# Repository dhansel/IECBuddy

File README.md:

# IECBuddy

IECBuddy is a USB plug-in for the [C64 RAD Expansion Unit](https://github.com/frntc/RAD), giving the RAD
access to the C64's IEC bus. The IECBuddy is based on my [IECDevice](https://github.com/dhansel/IECDevice)
and [VDrive](https://github.com/dhansel/VDrive) libraries, allowing the RAD to support various disk image 
formats (D64, G64, D71, D81) and fast-load protocols (JiffyDos, Epyx FastLoad, Final Cartridge 3, Action Replay 6,
DolphinDos and SpeedDos). Additionally, the IECBuddy acts as a virtual printer. Printed content can be viewed
on the C64 screen from within the RAD menu.

<br>
  <div align="center">

  </div>
<br>

The IECBuddy comes in four different variants, with differing amounts of components and build effort required:
  * [Barebones](IECBuddy-Barebones) (no PCB, use any RP2040/RP235x module)
  * [Micro](IECBuddy-Micro) (like Barebones but with a PCB and disk change button, requires a RP module pin-compatible with RP2040-One)
  * [Mini](IECBuddy-Mini) (like Micro but with a display and better bus interface, requires a RP module pin-compatible with RP2040-One)
  * [Max](IECBuddy-Max) (like Mini but with parallel cable connector, requires a RP module pin-compatible with Raspberry Pi Pico)

Of course a myriad versions of RP2040 and R235x modules exist. The PCBs for the IECBuddy Micro and Mini variants assume the pinout
of a [RP2040-One](https://www.amazon.com/RP2040-One-Pico-Like-Raspberry-Dual-Core-Processor/dp/B0BMM7SS99). The PCB for the
IECBuddy Max variant assumes the pinout of a Raspberry Pi Pico. The IECBuddy Barebones variant can work with any RP2040 or RP235x module.

To keep things a bit more succinct, in the folling "RP module" stands for "RP2040/RP235x module".

If you have a module with a pinout matching your preferred IECBuddy variant, first check if your module is listed in the UF2 table within the
[uploading the firmware](#uploading-the-firmware) section. If you cannot use one of the provided UF2 firmware files it should still
be fairly easy to [compile and upload](software/IECBuddy/README.md) the firmware yourself.

The IECBuddy stores files and disk images in the RP module's flash memory. One MB of flash memory is used for the
firmware itself, the remainder can be used for storing disk images. One MB of flash memory can hold about six D64 disk images.
Note that disk images can easily be transferred between the RAD and the IECBuddy so the IECBuddy does not need to hold all
your disk images at the same time.

The IECBuddy can plug directly into a RAD powered by a Raspberry Pi 3. If your RAD uses a Raspberry Pi Zero then 
you will need [an adapter cable](https://www.raspberrypi.com/products/micro-usb-male-to-usb-a-female-cable/) 
to connect the IECBuddy since the Zero only has a micro-USB OTG port.

To build an IECBuddy, select and build whichever variant appeals to you and then follow the instructions in the
[Uplodading the firmware](#uploading-the-firmware) section below.

## IECBuddy Barebones

The barebones variant is the simplest version, requiring no manufactured PCB. While the pictures shown here use
a [RP2040-One](https://www.amazon.com/RP2040-One-Pico-Like-Raspberry-Dual-Core-Processor/dp/B0BMM7SS99) module, any
RP module should work. Additionally you will need a Commodore [serial cable](https://www.c64-wiki.com/wiki/Serial_Port)
connector. Either solder the cable directly to the RP module or set it up on a breadboard:

<br>
  <div align="center">

  </div>
<br>

Connect the Commodore serial cable to the RP module as follows:

IEC Bus Pin | Signal   | RP module
------------|----------|-----------
1           | SRQ      | Not connected 
2           | GND      | GND
3           | ATN      | GPIO2
4           | CLK      | GPIO3 
5           | DATA     | GPIO4 
6           | RESET    | GPIO5 

Then [upload the IECBuddy Micro firmware](#uploading-the-firmware) to the RP module and you're good to go.
Downsides are that there is no display and no "Disk Change" button.
If you would like a "Disk Change" button, simply wire a pushbutton switch between pins GND and GPIO8 on the RP module.

Note that this connects the 5V IEC bus lines directly to the RP module inputs. There are varying
opinions online on whether or not this can damage the RP and/or whether the RP is
capable of properly driving the IEC bus lines (especially when multiple devices are connected).
In my testing I have not had any problems, even with multiple other devices connected. YMMV.

If you would prefer proper voltage conversion and line drivers then use the "Mini" version below.

## IECBuddy Micro

<br>
  <div align="center">

  </div>
<br>

If you would like a somewhat cleaner and more permanent build but still want to go with a very small
footprint and minimal component count, use the "IECBuddy Micro" variant. This PCB requires a RP
module that is pin-compatible with the RP2040-One. Check the [Uplodading the firmware](#uploading-the-firmware) 
section below to see which RP modules are supported.

You can either solder the serial cable directly onto the board (connections are labeled on the board) or solder a 
proper IEC connector onto the board and use a standard serial cable. This also comes with
space for a pushbutton switch. No display though.

The same caveats regarding voltage conversion and line drivers apply as described in the "Barebones" section above.

A Gerber file for PCB production can be downloaded [here](https://github.com/dhansel/IECBuddy/raw/refs/heads/main/hardware/IECBuddy-micro-gerber.zip).<br>
A PDF file with the schematics is available [here](https://github.com/dhansel/IECBuddy/raw/refs/heads/main/hardware/IECBuddy-micro-schematic.pdf).<br>
KiCad files for the board are [here](hardware/IECBuddy-micro).

You will need the following components (the given links are just suggestions, I do not get any kickbacks for them).

Designator | Component 
-----------|-----------
U1         | [RP2040-One](https://www.amazon.com/RP2040-One-Pico-Like-Raspberry-Dual-Core-Processor/dp/B0BMM7SS99)
SW1        | [Pushbutton Switch](https://www.digikey.com/en/products/detail/c-k/PTS645VH58-2-LFS/1146783)
IEC1       | [IEC Bus Connector (6 Pin)](https://www.aliexpress.us/item/3256807108500271.html)

You can skip the IEC1 connector if you solder the serial cable directly to the board (connections on the board are labeled).

## IECBuddy Mini

  <div align="center">

  </div>

The Mini variant is slightly larger than the Micro version and requires more components besides
the RP module. As a result it comes with the following features that are not present in the smaller versions:

First, it has space and connections on the PCB for a [1.3" TFT display](https://www.aliexpress.us/item/3256805899270213.html).
The display shows the currently mounted disk image as well as disk status and progress bars while loading.

Second, it uses 7406 and 74LVC04 ICs for voltage conversion and properly interfacing with and driving the Commodore IEC bus lines.
This is very similar to the way original hardware (like the 1541) interfaces to the IEC bus. It also protects the RP
from the possible overcurrent and overvoltage conditions described in the "Barebones" section above.

Like the Micro variant, this PCB requires a RP module that is pin-compatible with the RP2040-One. 
Check the [Uplodading the firmware](#uploading-the-firmware) section below to see which RP modules are supported.

A Gerber file for PCB production can be downloaded [here](https://github.com/dhansel/IECBuddy/raw/refs/heads/main/hardware/IECBuddy-mini-gerber.zip).<br>
A PDF file with the schematics is available [here](https://github.com/dhansel/IECBuddy/raw/refs/heads/main/hardware/IECBuddy-mini-schematic.pdf).<br>
KiCad files for the board are [here](hardware/IECBuddy-mini).

You will need the following components (the given links are just suggestions, I do not get any kickbacks for them).

Designator | Component 
-----------|-----------
R1,R2,R3,R4| [Resistor 1kOhm SMD0805](https://www.digikey.com/en/products/detail/stackpole-electronics-inc/RMCF0805FT1K00/1760090)
C1,C2      | [Ceramic Capacitor 100nF SMD0805](https://www.digikey.com/en/products/detail/kyocera-avx/KGM21NR71H104KT/563505)
U1         | [RP2040-One](https://www.amazon.com/RP2040-One-Pico-Like-Raspberry-Dual-Core-Processor/dp/B0BMM7SS99)
U2         | [74LVC04AD SOIC](https://www.digikey.com/en/products/detail/nexperia-usa-inc/74LVC04AD-118/946673)
U3         | [7406DR SOIC](https://www.digikey.com/en/products/detail/texas-instruments/SN7406DR/276661)
SW1        | [Pushbutton Switch](https://www.digikey.com/en/products/detail/c-k/PTS645VH58-2-LFS/1146783)
ST7789     | [TFT Display](https://www.aliexpress.us/item/3256805899270213.html)
IEC1       | [IEC Bus Connector (6 Pin)](https://www.aliexpress.us/item/3256807108500271.html)

Various components can be left out if desired:
  * You can leave out the IEC1 connector if you solder the serial cable directly to the board (connections on the board are labeled).
  * You can leave out the ST7789 display if you don't want a display.
  * If you don't want to use the IEC bus driver ICs then you can place solder on the JP1-JP5 solder jumpers and leave out R1-R4, C1, C2, U2 and U3 (in this case use the IECBuddyMicro.uf2 firmware).

I recommend uploading the firmware **before** soldering on the display. The display sits on top of the RP module, which
makes accessing the "Boot" button (required for firmware upload) tricky - still possible, but a bit fiddly.

## IECBuddy Max

The IECBuddy Max variant has a much larger PCB layout and uses a Raspberry Pi Pico (version 1 or 2).
It has all the features of the Mini version and additionally a second IEC port for daisy-chaining 
and a connector for a parallel cable to be used with Dolphin Dos and Speed Dos.
Descriptions on how to make a compatible parallel cable and user port connector can be found in
various places over the internet, for example
[here](https://github.com/dhansel/IECDevice/tree/main/hardware#user-port-breakout-board),
[here](https://github.com/svenpetersen1965/1541-parallel-adapter-SpeedDOS)
or [here](https://github.com/FraEgg/commodore-1541-parallel-port-adapter-c64-c128-speeddos-dolphindos)

  <div align="center">

  </div>

A Gerber file for PCB production can be downloaded [here](https://github.com/dhansel/IECBuddy/raw/refs/heads/main/hardware/IECBuddy-max-gerber.zip).<br>
A PDF file with the schematics is available [here](https://github.com/dhansel/IECBuddy/raw/refs/heads/main/hardware/IECBuddy-max-schematic.pdf).<br>
KiCad files for the board are [here](hardware/IECBuddy-max).

This PCB requires a RP module that is pin-compatible with the Raspberry Pi Pico. 
Check the [Uplodading the firmware](#uploading-the-firmware) section below to see which RP modules are supported.

You will need the following components (the given links are just suggestions, I do not get any kickbacks for them).

Designator | Component 
-----------|-----------
R1,R2,R3,R4| [Resistor 1kOhm SMD0805](https://www.digikey.com/en/products/detail/stackpole-electronics-inc/RMCF0805FT1K00/1760090)
C1,C2,C3   | [Ceramic Capacitor 100nF SMD0805](https://www.digikey.com/en/products/detail/kyocera-avx/KGM21NR71H104KT/563505)
U1         | [Raspberry Pi Pico](https://www.microcenter.com/product/661033/raspberry-pi-pico-microcontroller-development-board)
U2         | [74CBTD3861DW](https://www.digikey.com/en/products/detail/texas-instruments/SN74CBTD3861DW/378015)
U3         | [74LVC04AD SOIC](https://www.digikey.com/en/products/detail/nexperia-usa-inc/74LVC04AD-118/946673)
U4         | [7406DR SOIC](https://www.digikey.com/en/products/detail/texas-instruments/SN7406DR/276661)
Reset,DiskChg | [Pushbutton Switch](https://www.digikey.com/en/products/detail/same-sky-formerly-cui-devices-/TS02-66-60-BK-100-LCR-D/15634327)
ST7789     | [TFT Display](https://www.aliexpress.us/item/3256805899270213.html)
IEC1       | [IEC Bus Connector (6 Pin)](https://www.aliexpress.us/item/3256807108500271.html)
Parallel1, Parallel2 | [10-position IDC Connector](https://www.digikey.com/en/products/detail/on-shore-technology-inc/302-S101/2178422)

## Uploading the firmware

Pre-compiled versions of the firmware are available for all four versions of the IECBuddy and a variety of RP modules. 

If your RP module is included in the table below then programming is trivial. First, download the UF2 file appropriate for your IECBuddy variant and RP module
("---" in the table means "not supported because the RP module does not match the PCB"):

IECBuddy   | [RP2040-One](https://www.amazon.com/RP2040-One-Pico-Like-Raspberry-Dual-Core-Processor/dp/B0BMM7SS99) <br> (4MB flash) | [RP2350-One](https://www.ebay.com/itm/286217752456) <br> (4MB flash) | [TENSTAR RP2350](https://aliexpress.com/item/1005008622261552.html) <br> (16MB flash) | Pi Pico <br> (2MB flash) | Pi Pico 2 <br> (4MB flash) | [Purple Pico](https://de.aliexpress.com/item/1005005594351599.html) <br> (16MB flash)
-----------|------------|------------|-------------------|----------------|---------------------|---------------------
Barebones  | [UF2](https://github.com/dhansel/IECBuddy/raw/refs/heads/main/software/IECBuddyMicro2040One.uf2) | [UF2](https://github.com/dhansel/IECBuddy/raw/refs/heads/main/software/IECBuddyMicro2350One.uf2) | [UF2](https://github.com/dhansel/IECBuddy/raw/refs/heads/main/software/IECBuddyMicroTenstar2350.uf2) | [UF2](https://github.com/dhansel/IECBuddy/raw/refs/heads/main/software/IECBuddyMicroPico1.uf2) | [UF2](https://github.com/dhansel/IECBuddy/raw/refs/heads/main/software/IECBuddyMicroPico2.uf2) | [UF2](https://github.com/dhansel/IECBuddy/raw/refs/heads/main/software/IECBuddyMicroPurplePico.uf2)
Micro      | [UF2](https://github.com/dhansel/IECBuddy/raw/refs/heads/main/software/IECBuddyMicro2040One.uf2) | [UF2](https://github.com/dhansel/IECBuddy/raw/refs/heads/main/software/IECBuddyMicro2350One.uf2) | [UF2](https://github.com/dhansel/IECBuddy/raw/refs/heads/main/software/IECBuddyMicroTenstar2350.uf2) | --- | --- | ---
Mini       | [UF2](https://github.com/dhansel/IECBuddy/raw/refs/heads/main/software/IECBuddyMini2040One.uf2) | [UF2](https://github.com/dhansel/IECBuddy/raw/refs/heads/main/software/IECBuddyMini2350One.uf2)  | [UF2](https://github.com/dhansel/IECBuddy/raw/refs/heads/main/software/IECBuddyMiniTenstar2350.uf2)  | --- | --- | ---
Max        | --- | --- | --- | [UF2](https://github.com/dhansel/IECBuddy/raw/refs/heads/main/software/IECBuddyMaxPico1.uf2) | [UF2](https://github.com/dhansel/IECBuddy/raw/refs/heads/main/software/IECBuddyMaxPico2.uf2) | ---

Then:
  1) Connect the USB connector of the RP module to your computer in "boot" mode. This can be done in two ways:
     - Make the connection to the computer **while holding down the "Boot" button on the device**. Note that this can be tricky
       for the Mini version if you have already soldered the display since the display obstructs access to the RP2040-One.
     - Just connect the RP module without holding the "Boot" button down. This will register a new serial (COM) port on your computer.
       Download [SKTool.exe](https://github.com/dhansel/IECBuddy/raw/refs/heads/main/software/SKTool/SKTool.exe) and run it with the following parameters: `SKTool -p COMx boot` (where COMx is the new COM port).
       Alternatively, start a terminal program (e.g. TeraTerm, Putty or even the serial monitor in the Arduino IDE) and connect
       to the new COM port with a baud rate of 1200.
     As a result of either of these, your computer should now show a new external drive.
  2) Copy the downloaded UF2 file to the root directory of the new drive.
  3) Disconnect the RP module from your computer.

If your RP module is not included in the table above and/or you would like to compile the firmware yourself, instructions can be found [here](software/IECBuddy/README.md). 

## Usage

When it is connected to the RAD (via USB) and C64 (via serial cable), the IECBuddy behaves like a disk drive.
The initial device number is 8 but can be configured from within the RAD menu system.

The IECBuddy is based on the [IECDevice library](https://github.com/dhansel/IECDevice) and therefore supports the 
same fastload protocols: JiffyDos, Epyx FastLoad, Final Cartridge 3, Action Replay 6, DolphinDos and SpeedDos.
Games that use their own fastload protocols will likely not work, the IECBuddy will report error "M-E not supported"
and the on-board LED will blink quickly (5Hz as opposed to 2Hz for a regular error).

Loading the directory shows all files and disk images currently on the IECBuddy file system. You can use "CD"
to enter and exit disk images. If you have a DOS wedge (like in JiffyDos), `@CD:GAMES.D64` will enter the GAMES.D64
Disk image, `@CD/` will exit the image and go back to the top-level directory. If you do not have a DOS wedge, 
doing a `LOAD"GAMES.D64",8` will automatically switch into the GAMES.D64 disk image and load its directory,
`LOAD"/",8` will return to the top level.

If desired, a new disk image can be created by using the "N" command, for examplem, executing `@N:GAMES2.D64`
in the top-level dierctory will create a new disk image named GAMES2.D64.

Files (either PRG files or disk images) can be copied between the IECBuddy and the RAD's SD card via the RAD menu system.
To enter the [IECBuddy submenu](https://github.com/frntc/RAD#iecbuddy-submenu) on the RAD, press "I" within the RAD main menu.

<br>
  <div align="center">
  
  </div>
<br>

The IECBuddy also emulates a printer, more specifically a STAR NL-10 printer with device number 4. The STAR NL-10 was
compatible with Commodore MPS-801 commands as well as the EPSON FX-80 command set. Much of the existing C64 software
supports either one of these (if not specifically the NL-10) and should therefore be compatible.

After printing, enter the RAD menu to see a preview of the printout and/or copy a BMP or PDF version of the printed
content to the RAD's SD card.

<br>
  <div align="center">
  
  </div>
<br>

For more information on the RAD menu structure relating to the IECBuddy see [here](https://github.com/frntc/RAD#iecbuddy-submenu).

As an alternative to copying files via the RAD menu interface you can use connect the IECBuddy to your PC 
and use [SKTool](software/SKTool) to manage the files directly.

## Firmware revisions

The following IECBuddy firmware revisions have been released:

  - **1.0** (January 26, 2026)
    - Initial release
   
  - **1.01** (March 16, 2026)
    - Support ",A" (append) file open mode in main directory
    - If a file is created in the main directory and the file has a known extension (PRG, SEQ, D64, D71, D81, G64, G71) then do not add an additional .PRG extension
    - Fixed JiffyDos protocol timing issue when transmitting EOI in single-byte protocol
    - Fixed support of "XF-" and "XF+" commands in DolphinDos

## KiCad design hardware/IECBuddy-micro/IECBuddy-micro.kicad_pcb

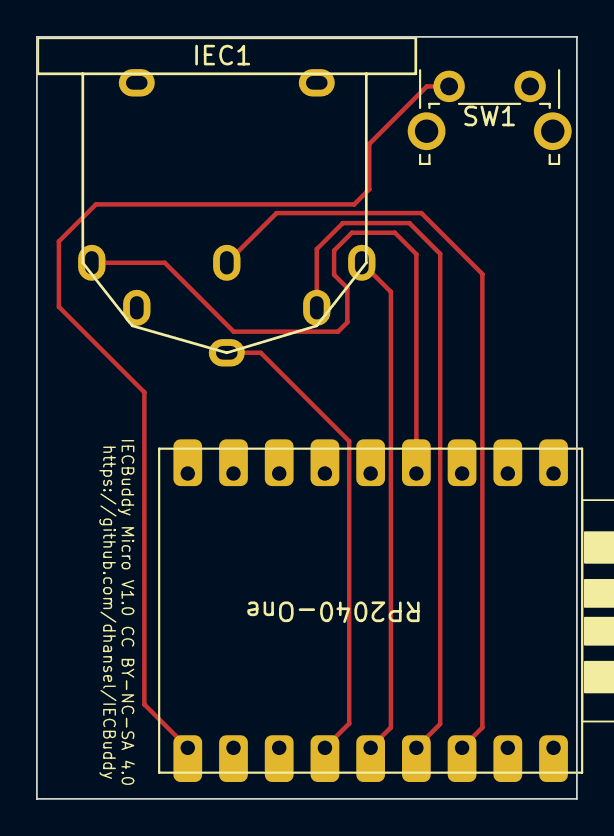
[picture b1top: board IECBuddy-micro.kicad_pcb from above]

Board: 2 copper layers, 30.0 x 42.3 mm, 5 parts (0 on the bottom side), 7 nets.

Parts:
IEC1: SDS-60J; C64_IEC
MH1, MH2: ZipTie; ZipTie_3.0mm
SW1: DskChg; SW_Tactile_SPST_Angled_PTS645Vx83-2LFS
U1: RP2040-One; RP2040-One-Sidesonly

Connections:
ATN: IEC1.3, U1.16 (GP2)
CLK: IEC1.4, U1.15 (GP3)
DATA: IEC1.5, U1.14 (GP4)
GND: IEC1.2, IEC1.E1 (GND), IEC1.E2 (GND__1), SW1.2, U1.2 (GND)
unnamed: SW1.1, U1.10 (GP8)
RST: IEC1.6, U1.13 (GP5)
SRQ: IEC1.1, U1.4 (GP29)

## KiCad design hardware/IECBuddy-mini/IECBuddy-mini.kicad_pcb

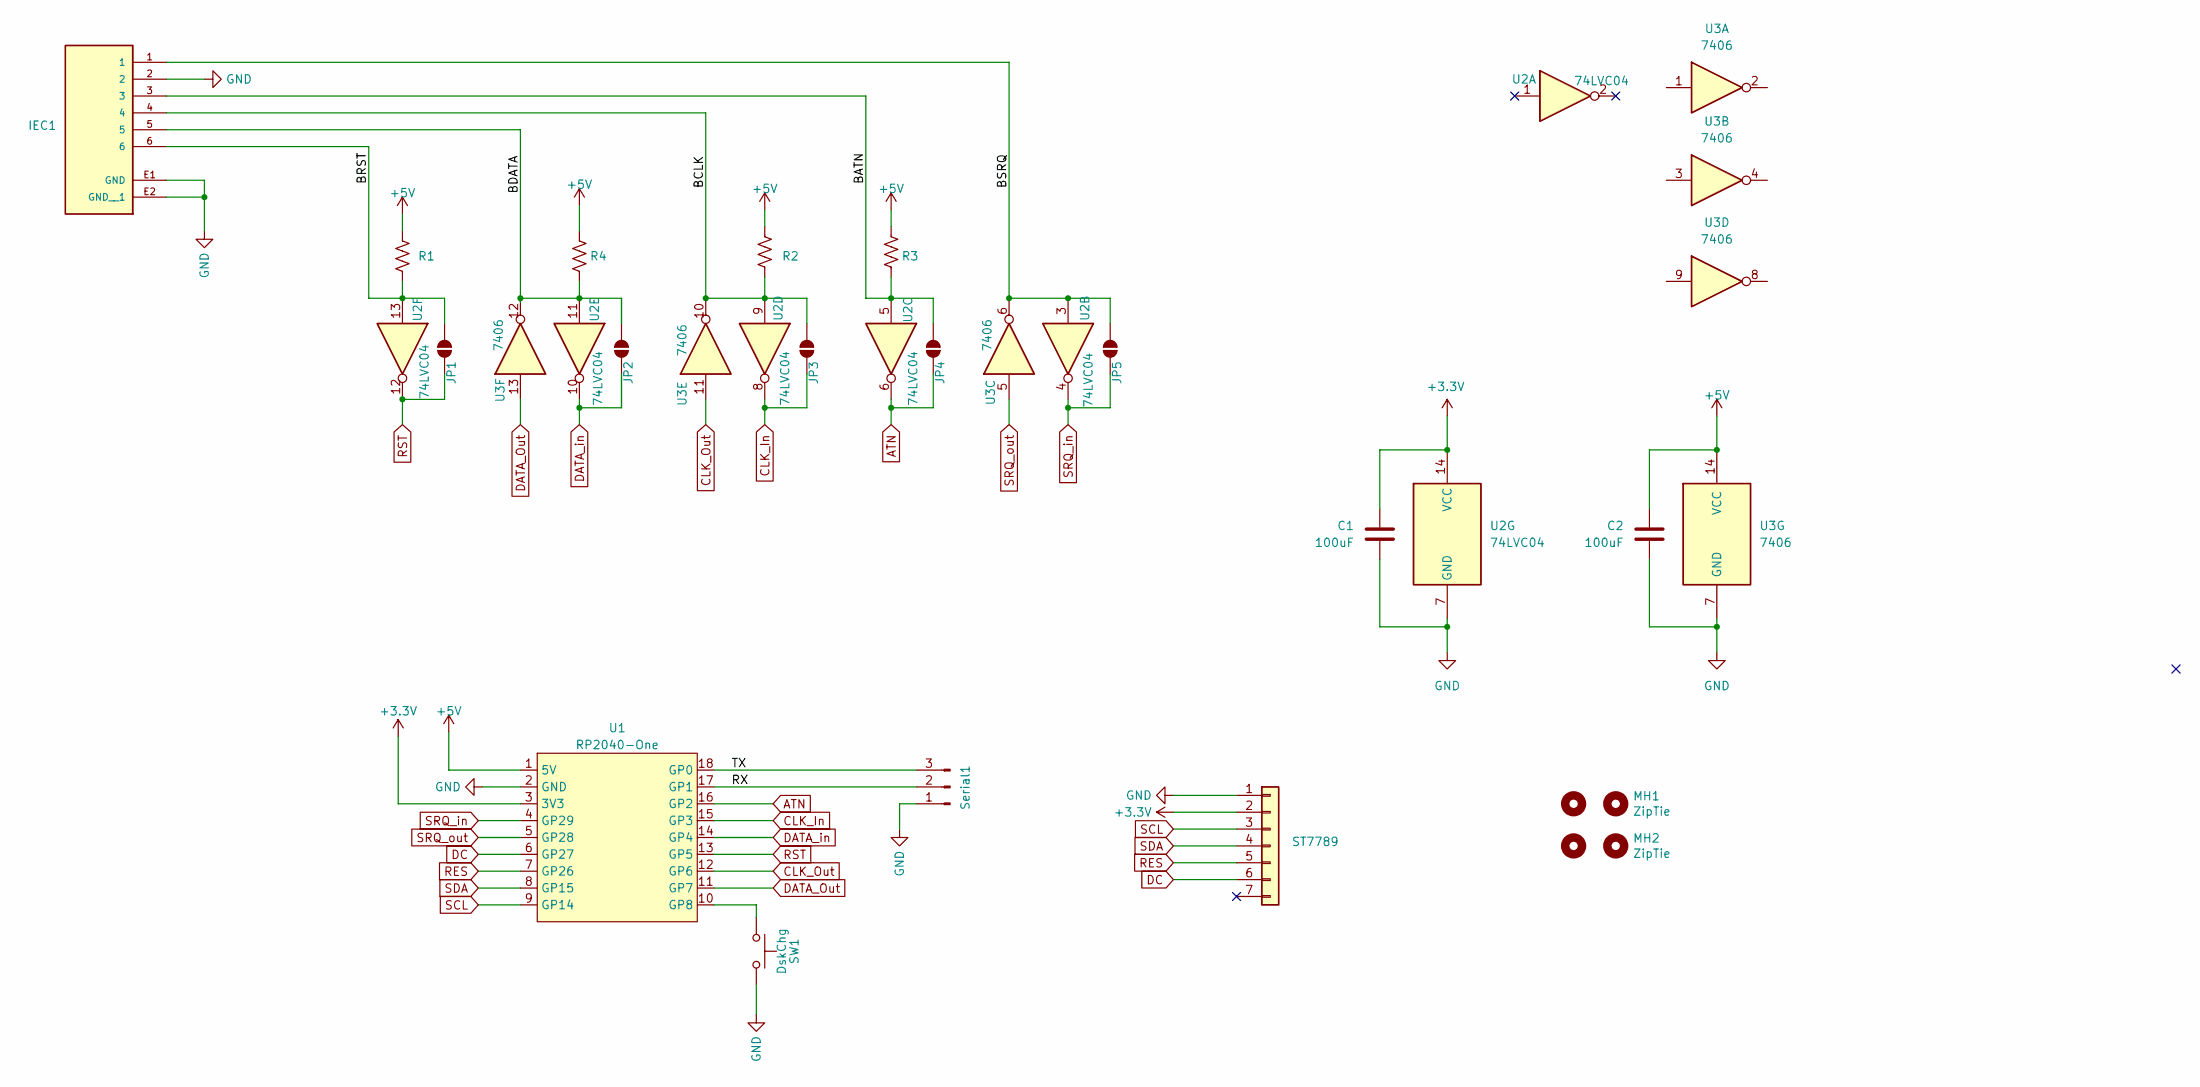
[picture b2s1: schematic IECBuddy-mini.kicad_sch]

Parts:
C1, C2: 100uF; C_0805_2012Metric_Pad1.18x1.45mm_HandSolder
H1, H2: MountingHole; MountingHole_3.2mm_M3
IEC1: SDS-60J; C64_IEC; PARTREV 1.06/02-13-2020
JP1, JP2, JP3, JP4, JP5: SolderJumper_2_Open; SolderJumper-2_P1.3mm_Open_Pad1.0x1.5mm
MH1, MH2: ZipTie; ZipTie_3.0mm
R1, R2, R3, R4: 1k; R_0805_2012Metric
ST7789: ST7789; PinHeader_1x07_P2.54mm_Vertical
SW1: DskChg; SW_Tactile_SPST_Angled_PTS645Vx83-2LFS
Serial1: Serial1; PinSocket_1x03_P2.54mm_Vertical
U1: RP2040-One; RP2040-One-Sidesonly
U2: 74LVC04; SOIC-14_3.9x8.7mm_P1.27mm
U3: 7406; SOIC-14_3.9x8.7mm_P1.27mm

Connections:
+3.3V: C1.1, ST7789.2, U1.3 (3V3), U2.14 (VCC)
+5V: C2.1, R1.1, R2.1, R3.1, R4.1, U1.1 (5V), U3.14 (VCC)
/BATN: IEC1.3, JP4.2 (B), R3.2, U2.5
/BCLK: IEC1.4, JP3.2 (B), R2.2, U2.9, U3.10
/BDATA: IEC1.5, JP2.2 (B), R4.2, U2.11, U3.12
/BRST: IEC1.6, JP1.2 (B), R1.2, U2.13
/BSRQ: IEC1.1, JP5.2 (B), U2.3, U3.6
/RX: Serial1.2, U1.17 (GP1)
/TX: Serial1.3, U1.18 (GP0)
ATN: JP4.1 (A), U1.16 (GP2), U2.6
CLK_In: JP3.1 (A), U1.15 (GP3), U2.8
CLK_Out: U1.12 (GP6), U3.11
DATA_Out: U1.11 (GP7), U3.13
DATA_in: JP2.1 (A), U1.14 (GP4), U2.10
DC: ST7789.6, U1.6 (GP27)
GND: C1.2, C2.2, IEC1.2, IEC1.E1 (GND), IEC1.E2 (GND__1), ST7789.1, SW1.2, Serial1.1, U1.2 (GND), U2.7 (GND), U3.7 (GND)
unnamed: SW1.1, U1.10 (GP8)
RES: ST7789.5, U1.7 (GP26)
RST: JP1.1 (A), U1.13 (GP5), U2.12
SCL: ST7789.3, U1.9 (GP14)
SDA: ST7789.4, U1.8 (GP15)
SRQ_in: JP5.1 (A), U1.4 (GP29), U2.4
SRQ_out: U1.5 (GP28), U3.5

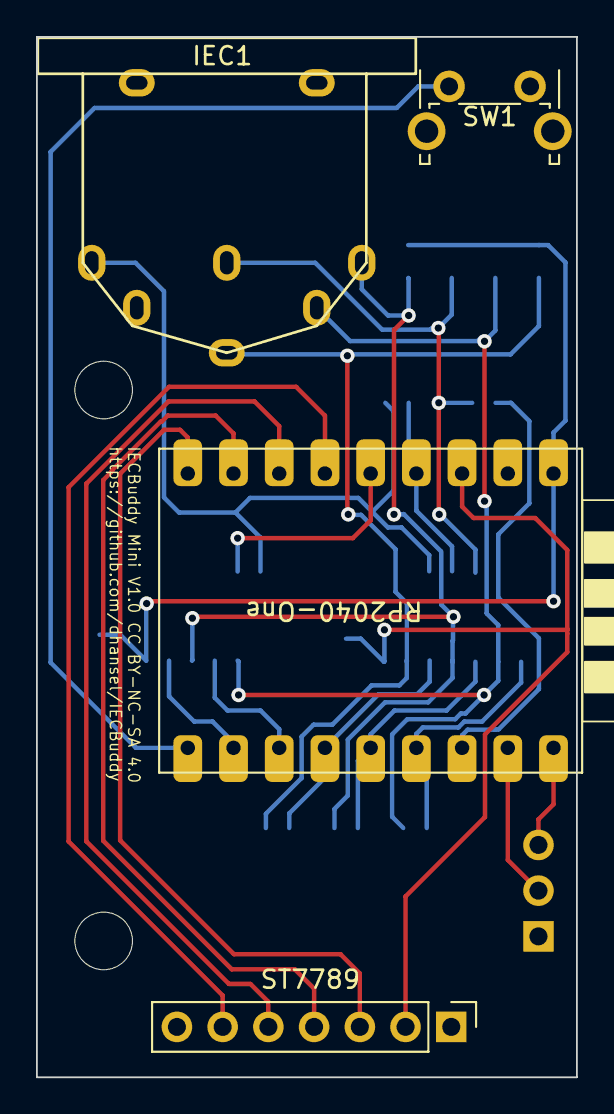
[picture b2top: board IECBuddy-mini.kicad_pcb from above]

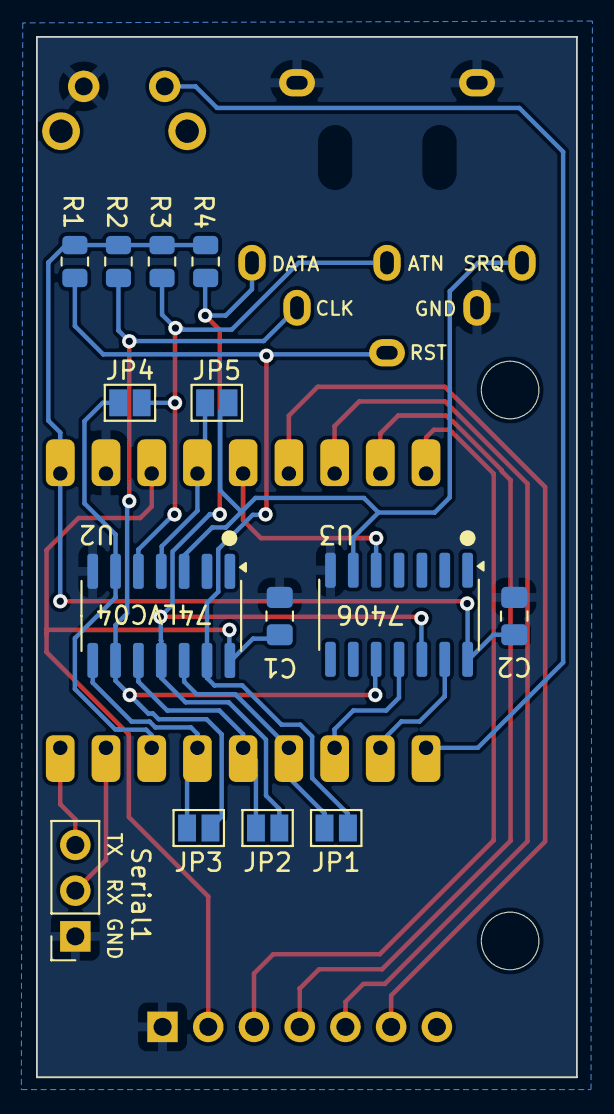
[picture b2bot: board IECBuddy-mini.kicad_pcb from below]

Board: 2 copper layers, 30.0 x 57.8 mm, 22 parts (14 on the bottom side), 23 nets.

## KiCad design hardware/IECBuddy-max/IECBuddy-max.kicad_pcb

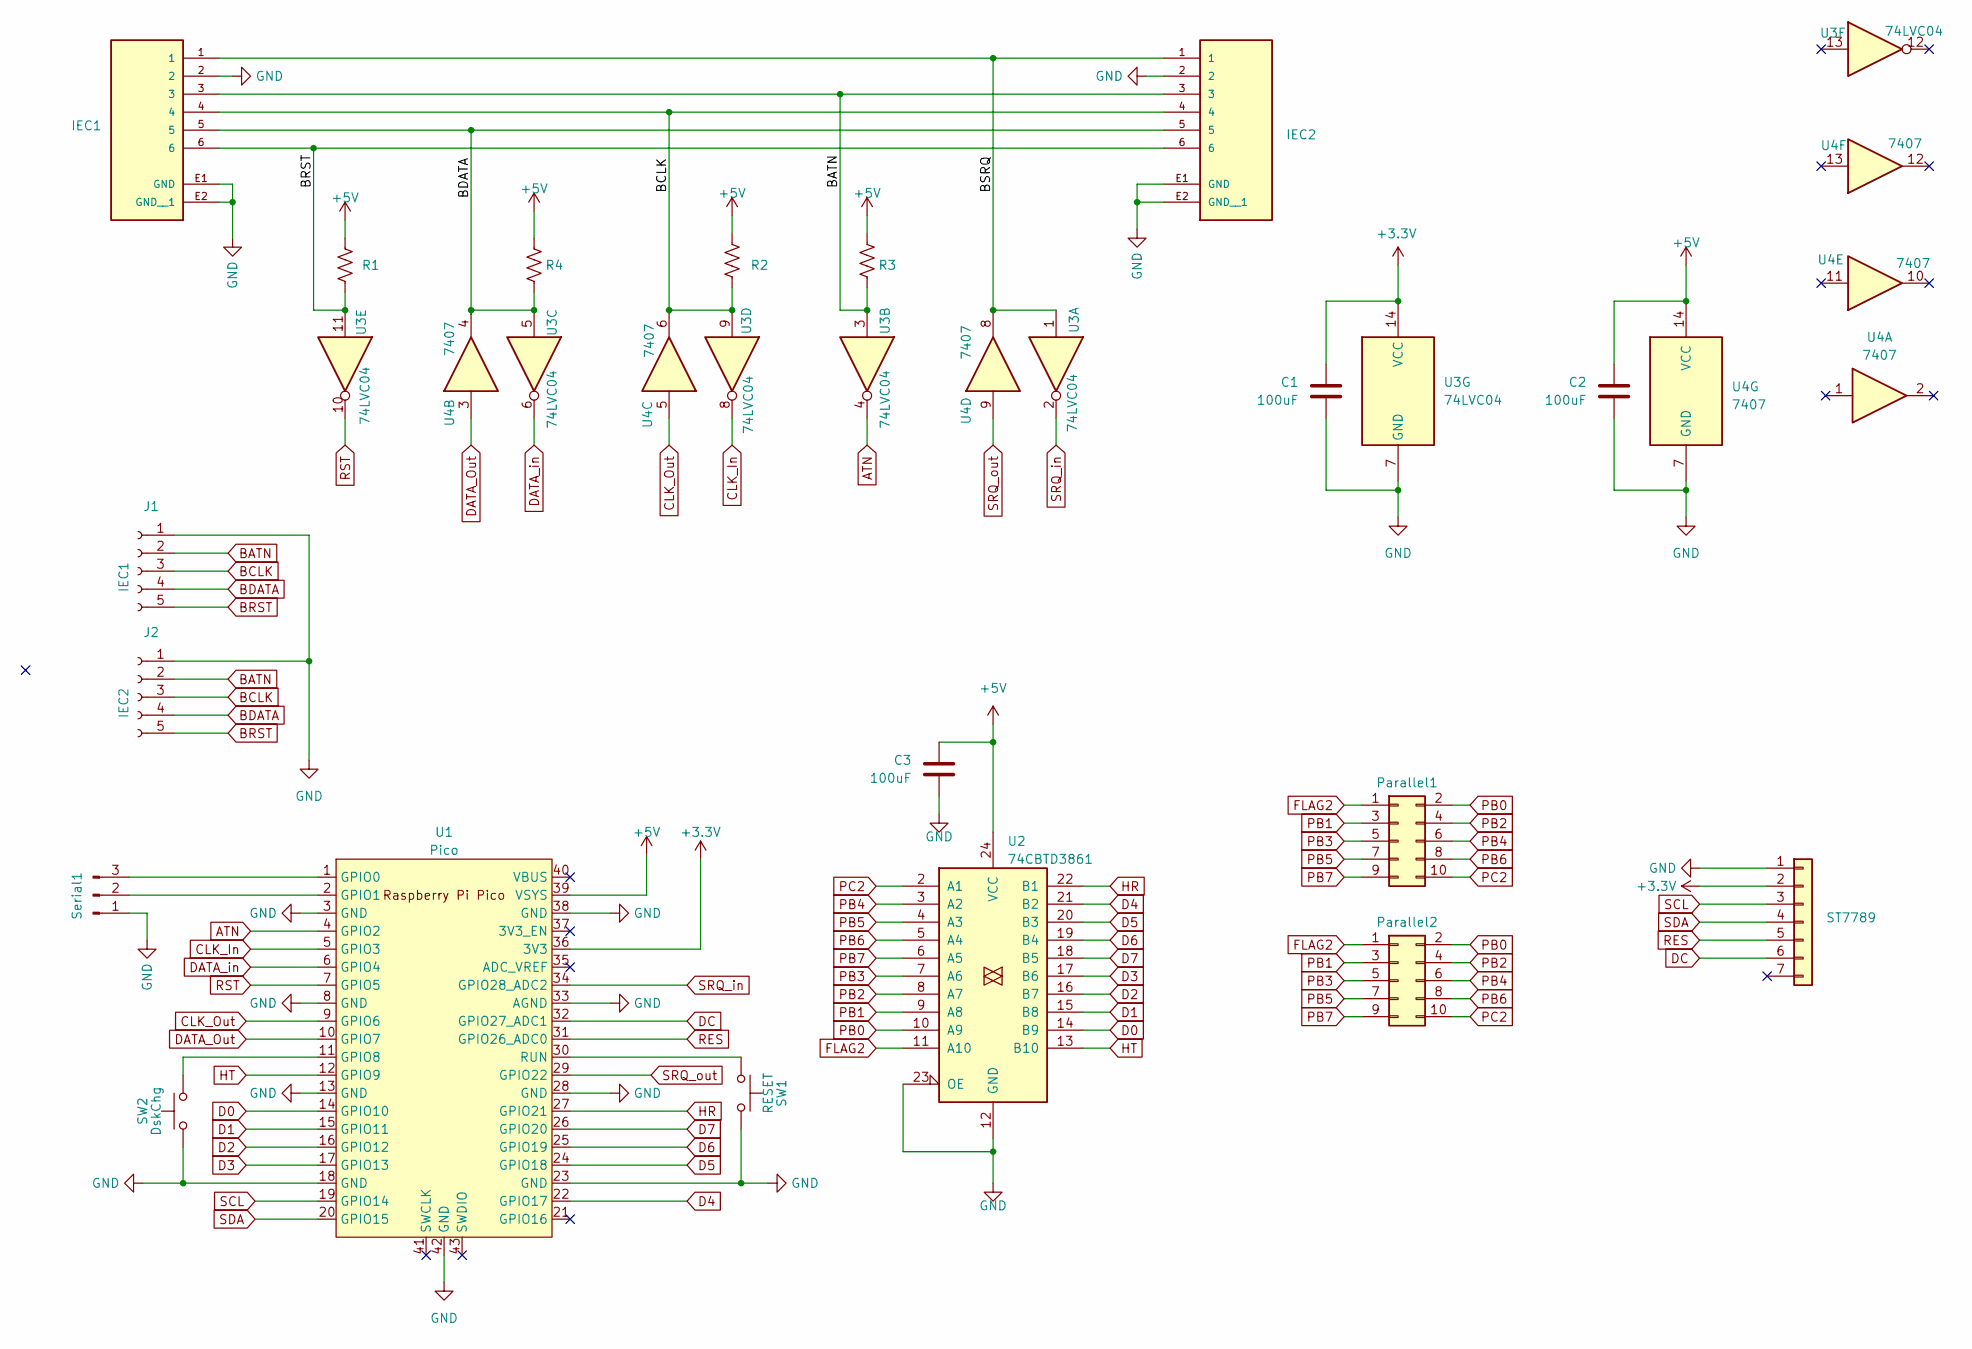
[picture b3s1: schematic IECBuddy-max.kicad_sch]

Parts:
C1, C2, C3: 100uF; C_0805_2012Metric_Pad1.18x1.45mm_HandSolder
IEC1, IEC2: SDS-60J; C64_IEC; PARTREV 1.06/02-13-2020
J1: IEC1; PinHeader_1x05_P2.54mm_Vertical
J2: IEC2; PinHeader_1x05_P2.54mm_Vertical
Parallel1: Parallel1; IDC-Header_2x05_P2.54mm_Vertical
Parallel2: Parallel2; IDC-Header_2x05_P2.54mm_Vertical
R1, R2, R3, R4: 1k; R_0805_2012Metric
ST7789: ST7789; PinHeader_1x07_P2.54mm_Vertical
SW1: RESET; SW_PUSH_6mm
SW2: DskChg; SW_PUSH_6mm
Serial1: Serial1; PinSocket_1x03_P2.54mm_Vertical
U1: Pico; RPi_Pico_SMD_TH
U2: 74CBTD3861; SOIC-24W_7.5x15.4mm_P1.27mm
U3: 74LVC04; SOIC-14_3.9x8.7mm_P1.27mm
U4: 7407; SOIC-14_3.9x8.7mm_P1.27mm

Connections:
+3.3V: C1.1, ST7789.2, U1.36 (3V3), U3.14 (VCC)
+5V: C2.1, C3.1, R1.1, R2.1, R3.1, R4.1, U1.39 (VSYS), U2.24 (VCC), U4.14 (VCC)
/BSRQ: IEC1.1, IEC2.1, U3.1, U4.8
ATN: U1.4 (GPIO2), U3.4
BATN: IEC1.3, IEC2.3, J1.2, J2.2, R3.2, U3.3
BCLK: IEC1.4, IEC2.4, J1.3, J2.3, R2.2, U3.9, U4.6
BDATA: IEC1.5, IEC2.5, J1.4, J2.4, R4.2, U3.5, U4.4
BRST: IEC1.6, IEC2.6, J1.5, J2.5, R1.2, U3.11
CLK_In: U1.5 (GPIO3), U3.8
CLK_Out: U1.9 (GPIO6), U4.5
D0: U1.14 (GPIO10), U2.14 (B9)
D1: U1.15 (GPIO11), U2.15 (B8)
D2: U1.16 (GPIO12), U2.16 (B7)
D3: U1.17 (GPIO13), U2.17 (B6)
D4: U1.22 (GPIO17), U2.21 (B2)
D5: U1.24 (GPIO18), U2.20 (B3)
D6: U1.25 (GPIO19), U2.19 (B4)
D7: U1.26 (GPIO20), U2.18 (B5)
DATA_Out: U1.10 (GPIO7), U4.3
DATA_in: U1.6 (GPIO4), U3.6
DC: ST7789.6, U1.32 (GPIO27_ADC1)
FLAG2: Parallel1.1, Parallel2.1, U2.11 (A10)
HR: U1.27 (GPIO21), U2.22 (B1)
HT: U1.12 (GPIO9), U2.13 (B10)
unnamed: Serial1.2, U1.2 (GPIO1)
unnamed: Serial1.3, U1.1 (GPIO0)
unnamed: SW2.2, U1.11 (GPIO8)
PB0: Parallel1.2, Parallel2.2, U2.10 (A9)
PB1: Parallel1.3, Parallel2.3, U2.9 (A8)
PB2: Parallel1.4, Parallel2.4, U2.8 (A7)
PB3: Parallel1.5, Parallel2.5, U2.7 (A6)
PB4: Parallel1.6, Parallel2.6, U2.3 (A2)
PB5: Parallel1.7, Parallel2.7, U2.4 (A3)
PB6: Parallel1.8, Parallel2.8, U2.5 (A4)
PB7: Parallel1.9, Parallel2.9, U2.6 (A5)
PC2: Parallel1.10, Parallel2.10, U2.2 (A1)
RES: ST7789.5, U1.31 (GPIO26_ADC0)
RST: U1.7 (GPIO5), U3.10
SCL: ST7789.3, U1.19 (GPIO14)
SDA: ST7789.4, U1.20 (GPIO15)
SRQ_in: U1.34 (GPIO28_ADC2), U3.2
SRQ_out: U1.29 (GPIO22), U4.9

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
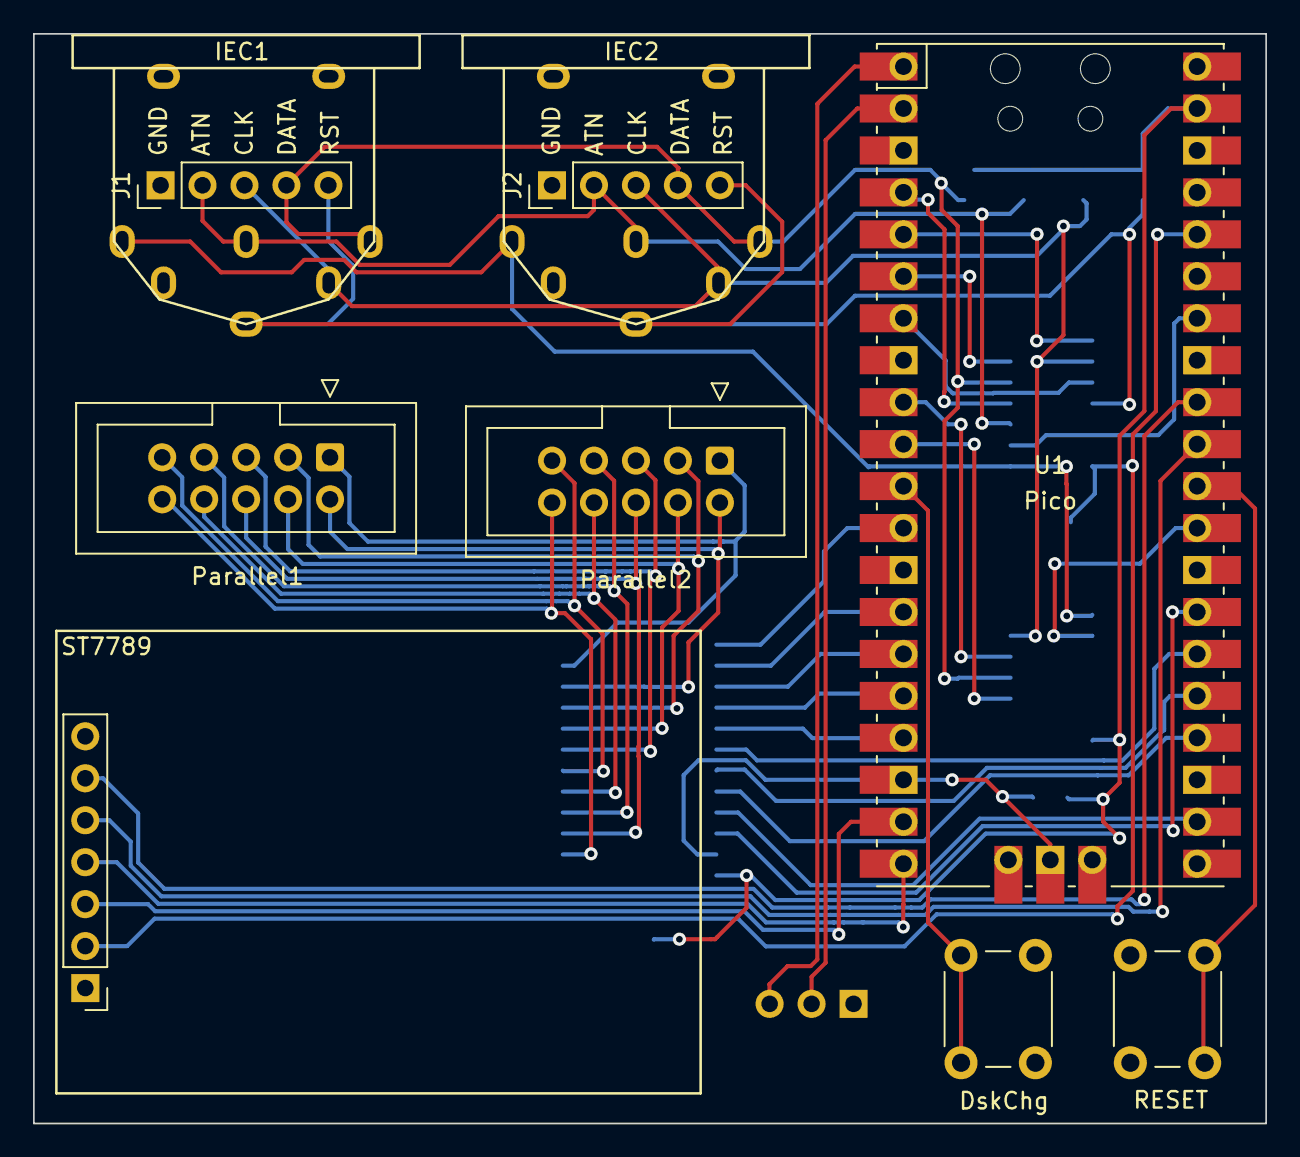
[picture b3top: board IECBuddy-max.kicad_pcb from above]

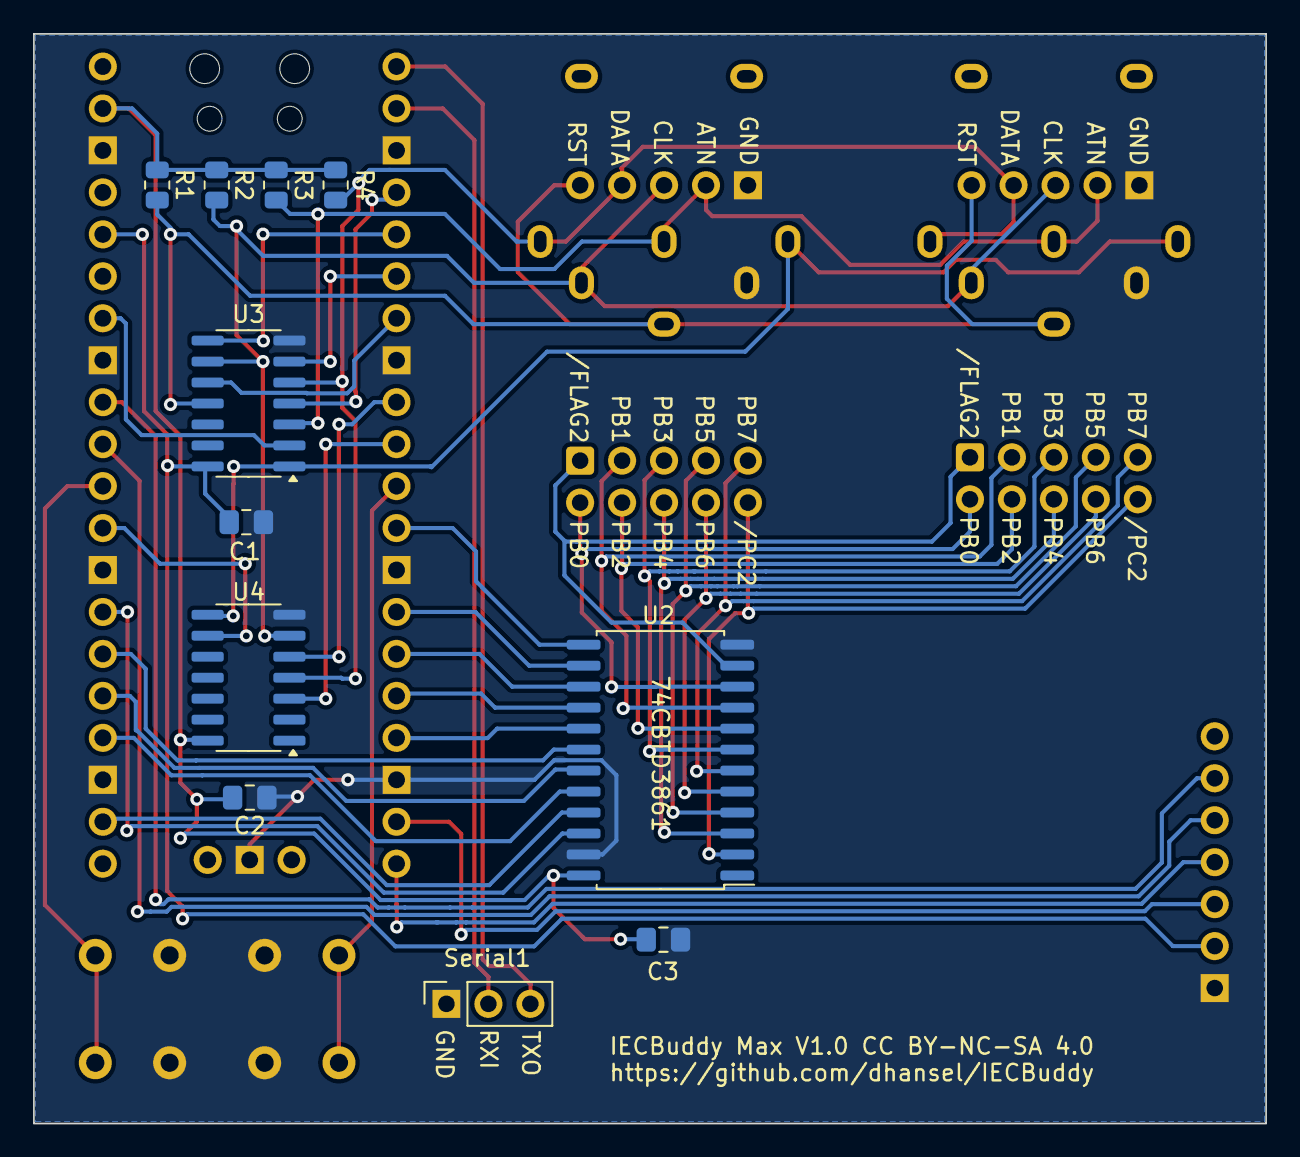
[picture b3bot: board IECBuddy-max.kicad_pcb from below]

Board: 2 copper layers, 74.6 x 66.0 mm, 21 parts (11 on the bottom side), 44 nets.

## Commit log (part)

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2025-03-22 Initial checkin
2025-03-27 Added configuration file and capability to change device number
2025-04-01 - added serial commands to mount/unmount a disk image and query currently mounted image - fixed issue where mounting an image within a ZIP file did not work - fixed issue where "N:name.d64" on top le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
2025-04-04 support using 74LS06/74LS07 line drivers for CLK/DATA lines
2025-04-04 Fixed rare time issue with PiPico when saving under Dolphin Dos and writing data to flash with LittleFS. Also fixed some issues with line driver support
2025-04-04 Fixed rare time issue with PiPico when saving under Dolphin Dos and writing data to flash with LittleFS.
2025-04-14 Moved debug pin for PiPico to GPIO28
2025-04-14 Added getFileNumBlocks function
2025-04-14 Added support for SSD1306 OLED display (SDA=GPIO20, SCL=GPIO21) and button for switching disk images (GPIO22).
2025-04-15 More work on display support
2025-04-24 Initial support for ST7789 display (currently disabled)
2025-04-24 Print drive status after executing command
2025-04-24 Always close and re-open image file after flushing memory data to force update of modification flag.
2025-04-24 Be more lenient about "CD" syntax: - ignore any characters between "CD" and first ":" (if one exists) - to exit from mounted image: CD.. CD/ CD< [left arrow] CD^ [up arrow]
2025-04-26 Various improvements: - any file with naming schema $*$ is invisible on IEC bus but accessible over serial protocol - added SET_CONFIG_VAL and GET_CONFIG_VAL commands to serial protocol - added DOS c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
2025-04-27 Fixed some issues with hidden files. Support (wildcard) patterns when loading directory.
2025-04-27 Added descriptions for recently added commands
2025-04-27 Removed Chip Select pin defition (not used, not needed)
2025-04-29 Keep protocol code in RAM (instead of flash) to prevent timing issues on some PiPico boards with (larger/slower) flash memory.
2025-05-02 Show progress animation during "save" (when total size is unknown)
2025-05-02 Fixed (recently introduced) issue with pattern matching when loading
2025-05-03 Allow wildcards in "CD" command. Produce better error message when CD fails but file exists (attempting to CD into a regular file).
2025-05-07 Fixed timing issue with SAVE operations under DolphinDos
2025-05-07 Allow CD from within one disk image into another if the path is prefixed by "/", i.e. if a disk image is currently mounted, "CD:OTHERIMAGE.D64" still does NOT work (because a disk image cannot be con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
2025-05-10 Added setup for line drivers (74LS07), enable "#define USE_LINE_DRIVERS" in src/IECDevice/IECConfig.h to use.
2025-05-17 Rearranged pin assignments so they work for PiPico and Waveshare RP2040-One boards. Consolidated all pin definitions into Pins.h header file
2025-05-17 Updated comments about unused pins
2025-05-18 Changed handling of file extensions. - Files received via USB _must_ have a 3-character extension (.XYZ), otherwise the receive operation fails - Files generated via IEC always get either a .PRG or .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
2025-05-19 Added logging for setconfig/getconfig
2025-05-19 Fixed issues with file extensions of file names longer than 16 characters
2025-05-19 Remove extension from file name for DIR (got broken in previous commit)
2025-05-20 If a "favlist" is defined in the config then pressing the DiskChange button now rotates through disk images defined in there.
2025-06-20 Support SpeedDos protocol and clean up parallel cable code
2025-07-14 Added printer support
2025-07-19 Added missing (new) files
2025-07-28 Fixed error when opening file if given file name starts with ":" (":" must be ignored in that case).
2025-07-28 Do not produce extra linefeed if control characters are received while at the end of a line.
2025-08-16 Added support for Final Cartridge 3 and Action Replay 6 fast-load protocols
2025-08-19 Do not produce a NO_CHANNEL when opening a file on a channel that is already open. Commodore drives just re-open the channel with the new file in that case. This caused errors when loading Mars Saga 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
2025-08-24 Brought up-to-date with recent IECDevice library changes (fixed some timing issues with FC3 and AR6 protocols)
2025-09-02 Fixed (unlikely) issue when closing printer data file
2025-09-02 Instead of having a bitmap take up RAM space in the Pico, dedicate a portion of the display to the image (never gets cleared or overwritten).
    When mounting a disk image NAME.D64, if a RGB565 bitmap file named 'NAME_WxH.BIN' exists (where W and H are width and height of the bitmap) then display that image.
2025-09-09 More work on displaying background images on ST7789, now supporting three different methods for buffering background image: on-disk, in-RAM or no buffering.
2025-09-19 Allocate memory in chunks of 4K instead of attempting to get one continuous region for the whole disk image. This is only slightly slower and avoids issues due to heap fragmentation.
    Also fixed bug when not enough memory is available and the disk image cannot
    be buffered in memory.
2025-09-19 Fixed potential compile error
2025-09-19 Reduced LED brightness on RP2040-One board
2025-09-20 Allow rotating display by setting config value "rotate" to 0,90,180 or 270. If config value "fsformat" is set to "1" then the LittleFS filesystem will be re-formatted at the next reboot. Moved displa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
2025-09-21 Fixed location of print "animation"
2025-09-21 Added REBOOT command
2025-09-25 Added compile-time option IEC_USE_INVERTED_INPUTS to support inverted inputs on the IEC lines.
2025-09-28 LOADing a disk image file mounts the disk image and loads its directory. LOADing ".." or "/" while a disk image is mounted unmounts the image and loads the SD card directory.
2025-10-01 Display file name using CBM font
2025-10-08 Fixed parser issue with B-R/B-W commands
2025-10-09 Fixed issue where BAM was not written out after B-A or B-F command
2025-10-09 Must not close file before checking its size (otherwise wrong size is returned)
2025-10-09 New parameter "diskflush" controls the timing of when changes in a disk image are written back to the disk image file on LittleFS: - diskflush<0: changes are only written back when disk image is unmo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
2025-10-10 When loading directory, use 0801h instead of 0401h as load address. While this is different from the stock C1541 behavior, it works better with using the "/" (load"..",8,1) shortcut on some cartridge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
2025-10-10 Reorganized code for flushing disk cache after writes. Now waits until drive is completely inactive (instead of just no more writes). Fixed issue where drive LED would stay on in some cases. Added "s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
2025-10-11 Fixed memory address for high byte of "free blocks" counter
2025-10-11 Fixed Epyx block read/write operations. Support setting disk address via M-W
2025-10-11 Minor debug logging improvement
2025-10-11 Fixed issue with B-P command
2025-10-11 Fixed buffering issue with U1 and B-R commands
2025-10-12 Always use white for displaying messages
2025-10-12 Removed unused code
2025-10-12 Show error message if a "M-E" (memory execute) command is received (not supported). Close current file and update display when "I" command is received.
2025-10-13 Support DolphinDos 40 track D64/G64 images (read and write). Fixed some issues with "V" command.
2025-10-22 Applied recent changes from IECDevice/VDrive libraries
2025-10-31 Ported recent improvements and bugfixes from IECDevice/VDrive libraries
2025-11-24 If PIN_IEC_CLK_OUT and PIN_IEC_DATA_OUT are defined then use inverted inputs and outputs (latest board revision usies 7406 for outputs and 74LVC04 for inputs)
2025-11-24 Ported recent changes from IECDevice/VDrive libraries
2025-11-29 Fixed bug in file name matching that caused "?" wildcard to not work
2025-12-02 Ported more recent updates from VDrive library
2025-12-03 make getFileNumBlocks() find first non-DEL file (like OPEN)
2025-12-03 Minor color change
2025-12-07 Added new SKTool to give users a better way to copy files from/to IECDevice:
    Usage: SKTool [-p COMx] dir|ls|rm|del|delete|cp|copy
    SKTool ls|dir [patterns] Display directory of files on IECDevice
    SKTool rm|del patterns Delete files matching pattern on IECDevice
    SKTool cp|copy [-f] patterns SK: Copy local files matching pattern to IECDevice
    SKTool cp|copy [-f] patterns dir Copy IECDevice files matching pattern to local directory dir
    SKTool cp|copy [-f] name1 SK:name2 Copy local file name1 to IECDevice as name2
2025-12-09 If a file name on LittleFS is more than 16 characters long then show a "*" as the last character.
2025-12-14 Immediately apply new "display rotation" setting without requiring reboot
2025-12-18 Immediately apply display rotation setting when issued as "CFG:ROTATE=..." through disk command channel.
2025-12-18 Ported recent improvements from IECDevice and VDrive libraries
2025-12-21 Code cleanup and file naming fixes
2026-01-11 Renamed IECSidekick64 -> IECBuddy
2026-01-11 Added KiCad files
2026-01-11 Add initial README.md for IECBuddy project
    Initial README
2026-01-12 More work on README
    Updated the README.md to improve clarity and organization of the IECBuddy variants and their components.
2026-01-12 More work on README
2026-01-12 More work on README
    Added links for compatible parallel cable descriptions.
2026-01-13 Added pictures
2026-01-13 Added images
    Added images
2026-01-13 More work on README
    Updated image links and text for the IECBuddy variants in the README.
2026-01-14 More work on README
    Corrected the number of IECBuddy variants from 'several' to 'four' and updated the list of variants accordingly.
2026-01-14 Fixed parameter issue for "rm" command
2026-01-14 Added picture
2026-01-14 More work on README
    Added an image and formatting to the README.
2026-01-14 Added pictures for Micro version
2026-01-14 More work on README
    Added images and description for the IECBuddy Micro variant.
2026-01-14 Added Gerber and Schematic files
2026-01-14 More work on README
    Updated links for Gerber files, schematics, and KiCad files for PCB production in the README.
2026-01-14 Moved software/firmware to separate folder
2026-01-14 Minor updates to some pics
2026-01-14 More work on README
    Updated details for the Barebones variant and clarified firmware uploading instructions.
2026-01-14 Add firmware compilation instructions to README
    Added instructions for compiling firmware from source.
2026-01-15 Added pre-compiled firmware files
2026-01-15 more work on README
    Added instructions for building the IECBuddy and uploading firmware.
2026-01-15 Updated for new directory structure, added "boot" command to SKTool
2026-01-15 Added README for SKTool usage
2026-01-16 If "diskflush" delay is not set, use 500ms delay.
2026-01-16 Removed debug output
2026-01-20 Added RAD menu screen shots
2026-01-20 More work in README
    Updated links and added references to the IECBuddy submenu in the README.
2026-01-20 More work on README
    Removed duplicate image link for IECBuddy in README.
2026-01-26 Added more UF2 files, renamed existing ones
2026-01-26 More work on README
    Updated references to RP2040 module compatibility and firmware upload instructions in the README.
2026-01-26 More work on README
    Updated the instructions for downloading UF2 files and clarified the programming process for RP2040 modules.
2026-01-26 Added more firmware images
2026-01-27 More work on README
    Added information about IECBuddy's support for fastload protocols and error reporting.
2026-03-17 Fixed "XF-" and "XF+" (disable/enable burst transfer mode) support in DolphinDos
2026-03-17 Fixed timing issue when waiting for host to confirm receipt after transmitting EOI in JiffyDOS single data byte transfers (must release DATA so we can detect DATA LOW).
2026-03-17 Improvements when opening files in main directory: - support append mode (",A") when opening a file - If a file is opened for writing and the file name has a known extension then do not append ".PRG"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
2026-03-17 Updated to latest version 1.01

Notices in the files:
hardware/IECBuddy-max/IECBuddy-max.kicad_pcb:
IECBuddy Max V1.0 CC BY-NC-SA 4.0
hardware/IECBuddy-micro/IECBuddy-micro.kicad_pcb:
IECBuddy Micro V1.0 CC BY-NC-SA 4.0
hardware/IECBuddy-mini/IECBuddy-mini.kicad_pcb:
IECBuddy Mini V1.0 CC BY-NC-SA 4.0
